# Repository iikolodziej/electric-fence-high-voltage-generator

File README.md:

# electric-fence-high-voltage-generator
electric fence / high voltage generator

# schematic

# pcb

# some scrap parts

# first tests

# development

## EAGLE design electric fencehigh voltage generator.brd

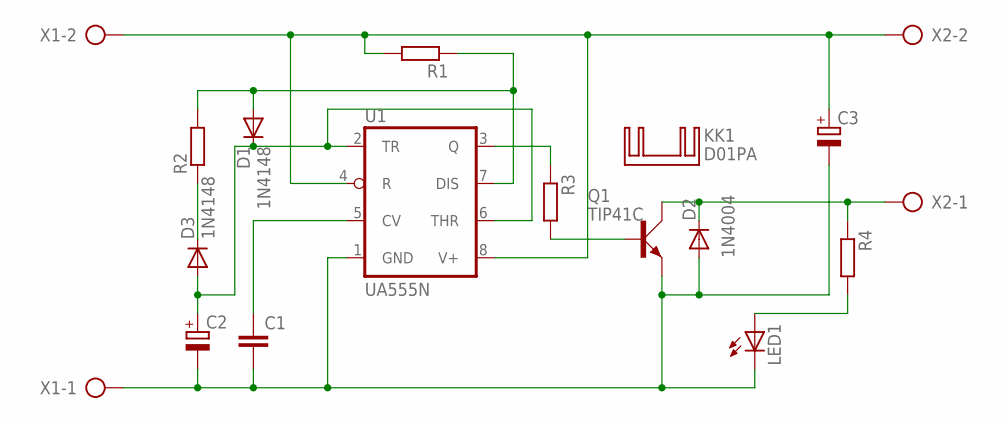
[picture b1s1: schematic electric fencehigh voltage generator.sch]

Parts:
C1: C-EU050-030X075; C050-030X075
C2, C3: CPOL-EUE2.5-5; E2,5-5
D1, D3: 1N4148; DO35-7
D2: 1N4004; DO41-10
KK1: D01PA
LED1: LED5MM
Q1: TIP41C; TO220AV
R1, R2, R4: R-EU_0207/10; 0207/10
R3: R-EU_0207/15; 0207/15
U1: UA555N; DIL08
X1, X2: AK300/2

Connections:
unnamed: C3.+, R1.2, U1.4 (R), U1.8 (V+), X1.2, X2.2
unnamed: R3.1, U1.3 (Q)
unnamed: Q1.B, R3.2
unnamed: D2.C, Q1.C, R4.1, X2.1
unnamed: C2.+, D1.C, D3.A, U1.2 (TR), U1.6 (THR)
unnamed: D1.A, R1.1, R2.2, U1.7 (DIS)
unnamed: D3.C, R2.1
unnamed: LED1.A, R4.2
unnamed: C1.2, C2.-, C3.-, D2.A, LED1.K (C), Q1.E, U1.1 (GND), X1.1
unnamed: C1.1, U1.5 (CV)

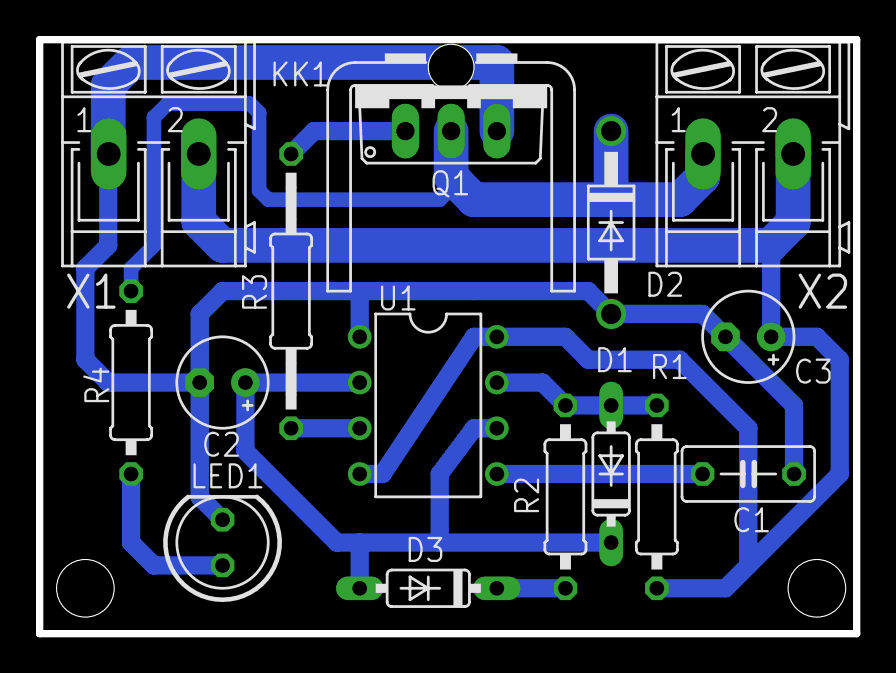
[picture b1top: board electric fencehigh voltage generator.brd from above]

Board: 2 copper layers, 45.4 x 33.0 mm, 16 parts (0 on the bottom side), 10 nets.

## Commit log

2023-10-19 add design files
